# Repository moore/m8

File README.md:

# m8

### Button Use
```mermaid
stateDiagram
    direction LR
    Sleep --> Status: Single
    Status --> Conversation: Double
    Status --> Stimulate: Long
    Status --> Status: Single
    Conversation --> Conversation: Single
    Stimulate --> Stimulate: Single
    Timeout --> Sleep
```

### Happiness
```mermaid
stateDiagram
    Status --> Ignore: Decrease
    Sleep --> Ignore: Decrease
    Sleep --> Status: Increase
    Status --> Game
    Game --> Status: Increase

```

### Pet Game
```mermaid
stateDiagram
    Status --> Pet: Click
    Pet --> Status
    OverStimulated: Over Stimulated
    Status --> OverStimulated: Click
    OverStimulated --> Status: Decrease Happiness

```

### Conversation F
Repeats three times.
```mermaid
stateDiagram
    direction LR
    [*] --> Pattern
    Pattern --> Response: Clicks
    Response --> Pattern
```
### Conversation M
Repeats three times.
```mermaid
stateDiagram
    direction LR
    [*] --> Pattern
    Pattern --> Interruption: Click
    Interruption --> Mad
    Mad --> Pattern
    Pattern --> Acknowledge: Click
    Acknowledge --> Pattern
    Pattern --> Ignore
    Ignore --> Mad
```

### Stimulate F
```mermaid
stateDiagram
    direction LR
    [*] --> Show
    Show --> Delay
    Delay --> Stimulate: Click
    Stimulate --> Show
    Stimulate --> Rainbow: Satisfied
    Rainbow --> Annoyed: Click
    Annoyed --> Rainbow
```

### Stimulate M
```mermaid
stateDiagram
    direction LR
    [*] --> Ready
    Ready --> Ready: Click
    Ready --> Rainbow: After 15 Clicks
```

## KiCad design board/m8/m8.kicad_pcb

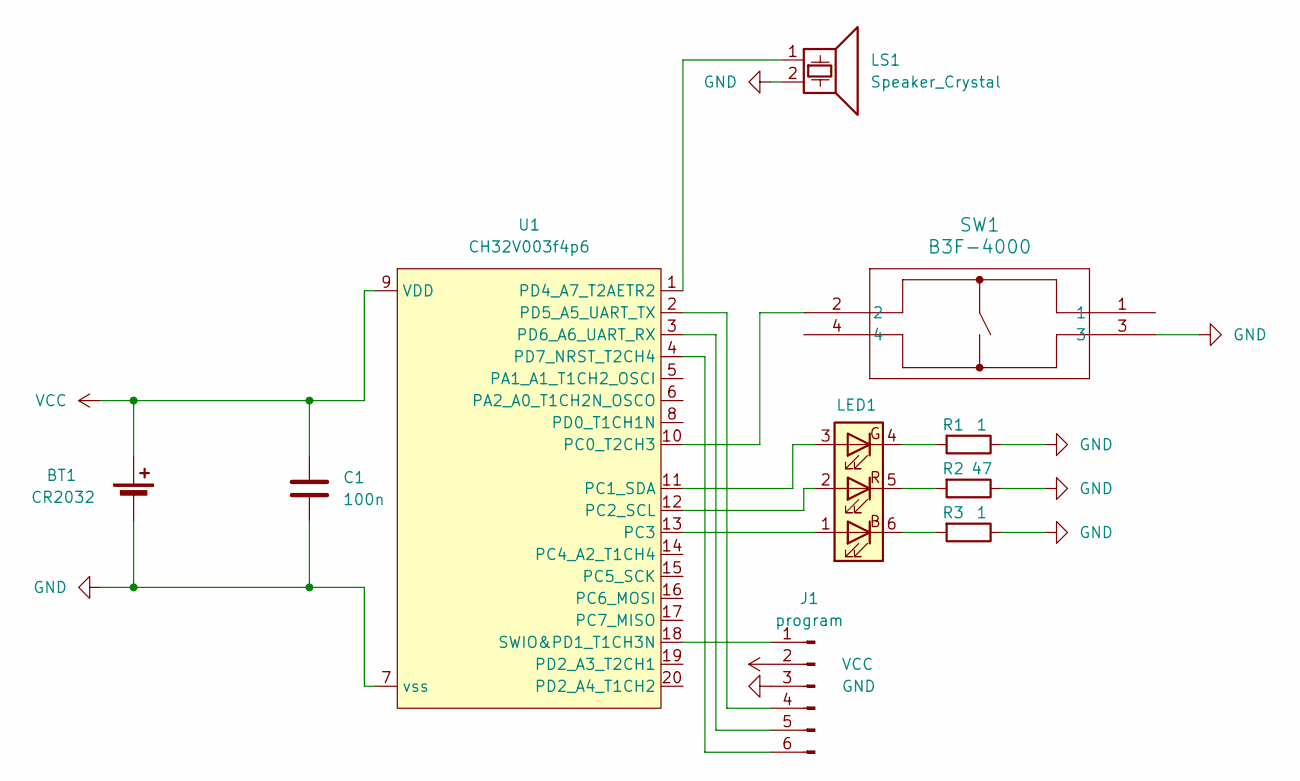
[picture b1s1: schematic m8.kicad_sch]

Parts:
BT1: CR2032; BatteryHolder_m8_1x2032
C1: 100n; C_0805_2012Metric_Pad1.18x1.45mm_HandSolder
J1: program; PinHeader_1x06_P2.54mm_Vertical
LED1: LED_RGB_5050-6
LS1: Speaker_Crystal; Buzzer_12x8.4RM6.6
R1, R3: 1; R_0805_2012Metric_Pad1.20x1.40mm_HandSolder
R2: 47; R_0805_2012Metric_Pad1.20x1.40mm_HandSolder
SW1: B3F-4000; SW_B3F-4000_OMR
U1: CH32V003f4p6; TSSOP-20_4.4x6.5mm_P0.65mm

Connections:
GND: BT1.2 (-), C1.2, J1.3, LS1.2, R1.1, R2.1, R3.1, SW1.3, U1.7 (vss)
unnamed: J1.1, U1.18 (SWIO&PD1_T1CH3N)
unnamed: J1.4, U1.2 (PD5_A5_UART_TX)
unnamed: J1.5, U1.3 (PD6_A6_UART_RX)
unnamed: J1.6, U1.4 (PD7_NRST_T2CH4)
unnamed: LED1.1 (BA), U1.13 (PC3)
unnamed: LED1.6 (BK), R3.2
unnamed: LED1.3 (GA), U1.11 (PC1_SDA)
unnamed: LED1.4 (GK), R1.2
unnamed: LED1.2 (RA), U1.12 (PC2_SCL)
unnamed: LED1.5 (RK), R2.2
unnamed: SW1.2, U1.10 (PC0_T2CH3)
unnamed: LS1.1, U1.1 (PD4_A7_T2AETR2)
VCC: BT1.1 (+), C1.1, J1.2, U1.9 (VDD)

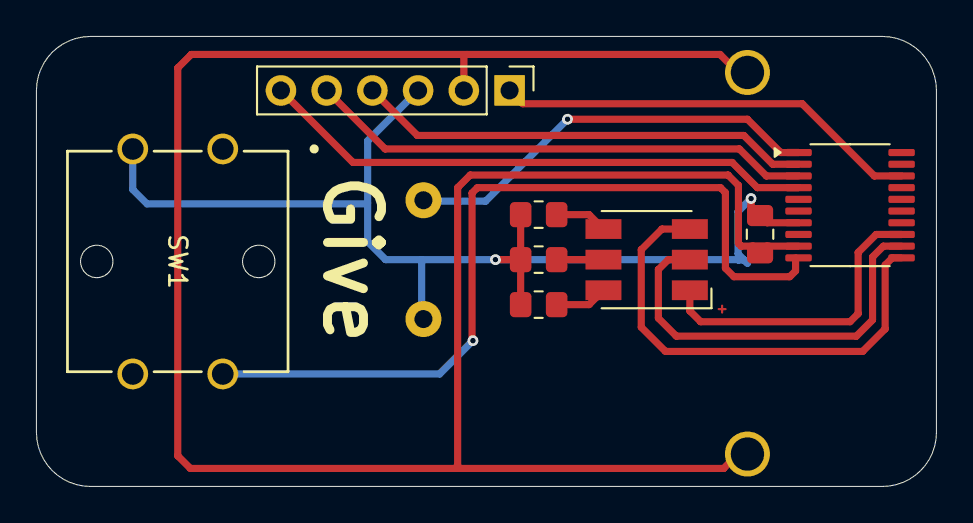
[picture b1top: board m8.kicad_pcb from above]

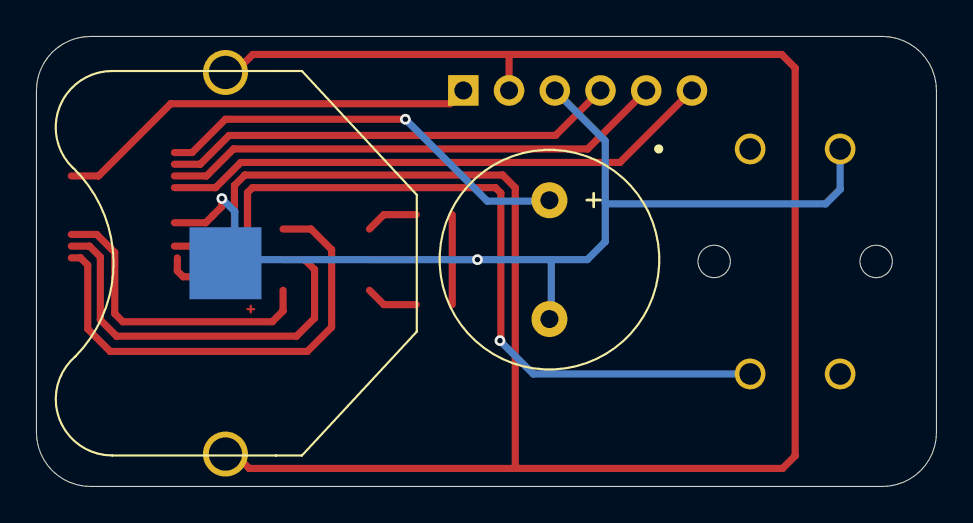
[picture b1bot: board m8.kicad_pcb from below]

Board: 2 copper layers, 50.0 x 25.0 mm, 10 parts (2 on the bottom side), 14 nets.

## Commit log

2024-05-05 Async test and state docs
2024-05-19 added ch32v003fun implmentation (initial)
2024-05-19 updated .gitignore for ch32v003 and removed rust bits
2024-05-19 renamed file to m8.c
2024-05-19 moved macros to m8.h
2024-05-20 got sleep waiting for intrupt working
2024-05-26 updating board
2024-05-26 untract file with local paths
2024-05-26 Found bugs fixed them!
2024-05-26 tweeks
2024-05-26 moved all power lines to 0.4mm
2024-05-26 cosmetic changes
2024-05-26 more cosmetic changes
2024-05-26 increase trace for speaker
2024-05-26 increased the size of all tracks to 0.4mm
2024-05-26 small cosmetic tweek
2024-05-26 increase clearances
2024-05-27 move LED down
2024-05-27 updated ignore
2024-05-27 small tweeks
2024-05-29 rev2 with sugestions from Chip
2024-05-29 fixed bugs!
2024-05-31 set all pins low instead of floating so that we reach lowest power draw in stand by
2024-06-09 got fancy anamated lights started
2024-06-09 update to have envlope for led anamation
2024-06-10 remove "magic" delay and tune the anamation
2024-06-25 button statis are mostly working still gets in to error states and needs some clean up but it's worth saving this state
2024-08-31 added hardware debug and deleted a bunch of unused code
